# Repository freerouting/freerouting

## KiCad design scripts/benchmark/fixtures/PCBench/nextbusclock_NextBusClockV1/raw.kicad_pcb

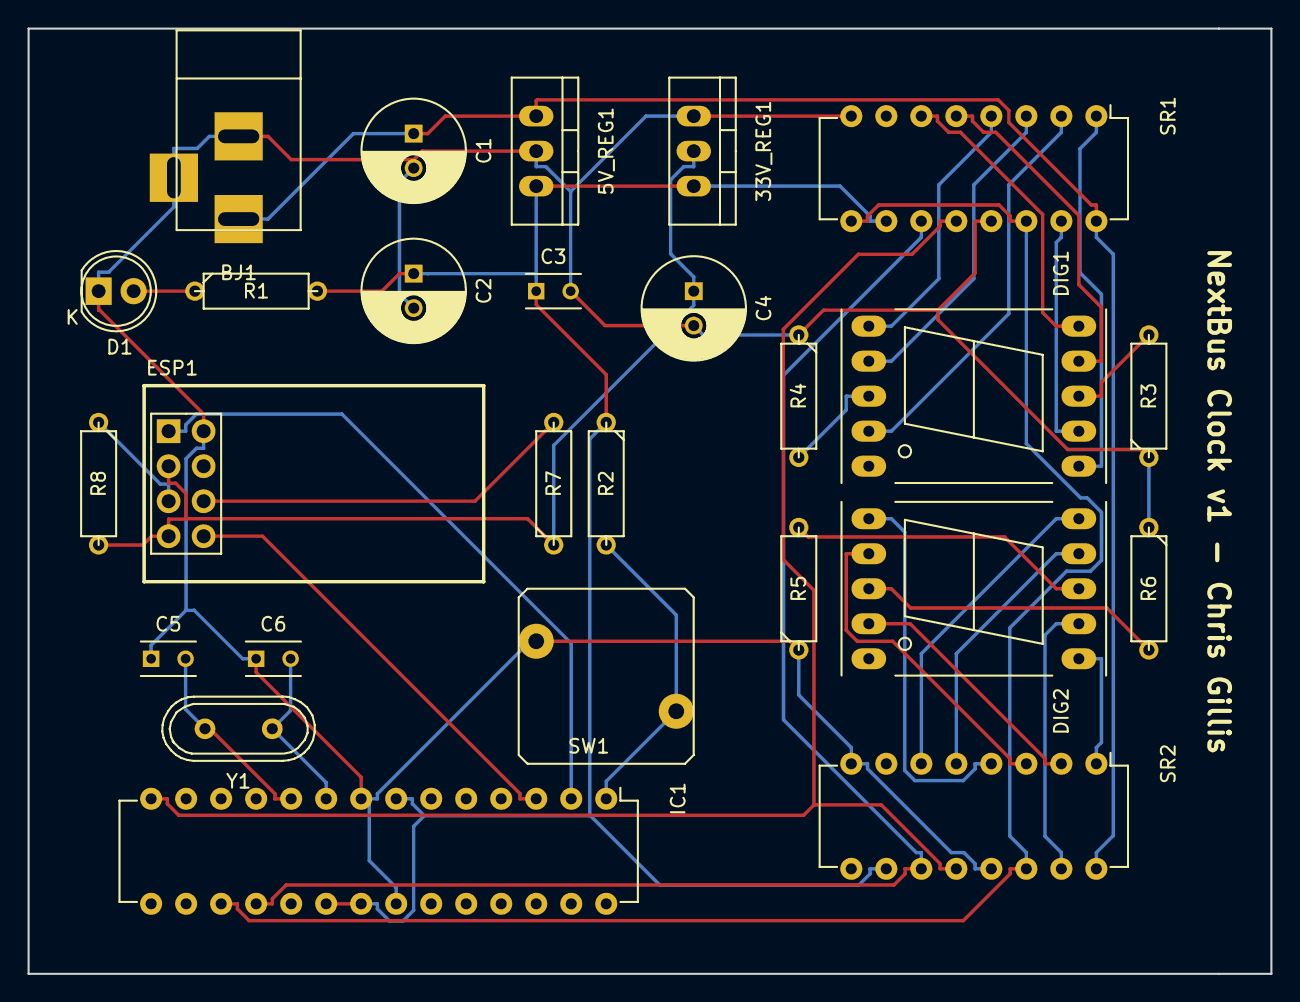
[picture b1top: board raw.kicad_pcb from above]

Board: 2 copper layers, 90.2 x 68.6 mm, 26 parts (0 on the bottom side), 33 nets.

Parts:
5V_REG1: LM7805; TO-220_Neutral123_Vertical
33V_REG1: LD1117V33; TO-220_Neutral123_Vertical
BJ1: BARREL_JACK
C1: 10uF; C_Radial_D7.5_L11.2_P2.5
C2: 1uF; C_Radial_D7.5_L11.2_P2.5
C3: 0.1uf; C_Rect_L4_W2.5_P2.5
C4: 10uf; C_Radial_D7.5_L11.2_P2.5
C5, C6: 22pF; C_Rect_L4_W2.5_P2.5
D1: PWR_LED; LED-5MM
DIG1, DIG2: LTS-6980HR; 7SegmentLED_LTS6760_LTS6780
ESP1: ESP-01
IC1: ATMEGA328-P; DIP-28_W7.62mm
R1: 1k; R3-5
R2, R7, R8: 10k; R3-5
R3, R4, R5, R6: 470; R3-5
SR1, SR2: 74HC595; DIP-16_W7.62mm
SW1: SW_PUSH
Y1: 16MHz; Crystal_HC49-U_Vertical

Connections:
/5V_PWR: 5V_REG1.3, 33V_REG1.3, C2.1, C3.1, IC1.7, IC1.20, IC1.21, R1.2, R2.1, SR1.10, SR2.10
/33V_PWR: 33V_REG1.2, C4.1, ESP1.3, ESP1.7, R7.1, R8.2
/ESP_RX: ESP1.8, IC1.3
/ESP_TX: ESP1.1, IC1.2
/SR_CLOCK: IC1.18, SR1.11, SR2.11
/SR_DATA: IC1.17, SR1.9, SR1.14, SR2.14
/SR_LATCH: IC1.14, SR1.12, SR2.12
GND: 5V_REG1.2, 33V_REG1.1, BJ1.2, BJ1.3, C1.2, C2.2, C3.2, C4.2, C5.1, C6.1, D1.1, ESP1.2, IC1.8, IC1.22, R3.1, R4.1, R5.1, R6.1, SR1.8, SR1.13, SR2.8, SR2.13, SW1.2
unnamed: C5.2, IC1.10, Y1.2
unnamed: C6.2, IC1.9, Y1.1
unnamed: D1.2, R1.1
unnamed: DIG1.1, SR1.4
unnamed: DIG1.2, SR1.3
unnamed: DIG1.3, R4.2
unnamed: DIG1.4, SR1.2
unnamed: DIG1.6, SR1.1
unnamed: DIG1.7, SR1.15
unnamed: DIG1.8, R3.2
unnamed: DIG1.9, SR1.5
unnamed: DIG1.10, SR1.6
unnamed: DIG2.1, SR2.4
unnamed: DIG2.2, SR2.3
unnamed: DIG2.3, R6.2
unnamed: DIG2.4, SR2.2
unnamed: DIG2.6, SR2.1
unnamed: DIG2.7, SR2.15
unnamed: DIG2.8, R5.2
unnamed: DIG2.9, SR2.5
unnamed: DIG2.10, SR2.6
unnamed: ESP1.5, R8.1
unnamed: ESP1.6, R7.2
unnamed: IC1.1, R2.2, SW1.1
VCC: 5V_REG1.1, BJ1.1, C1.1, SR1.16, SR2.16

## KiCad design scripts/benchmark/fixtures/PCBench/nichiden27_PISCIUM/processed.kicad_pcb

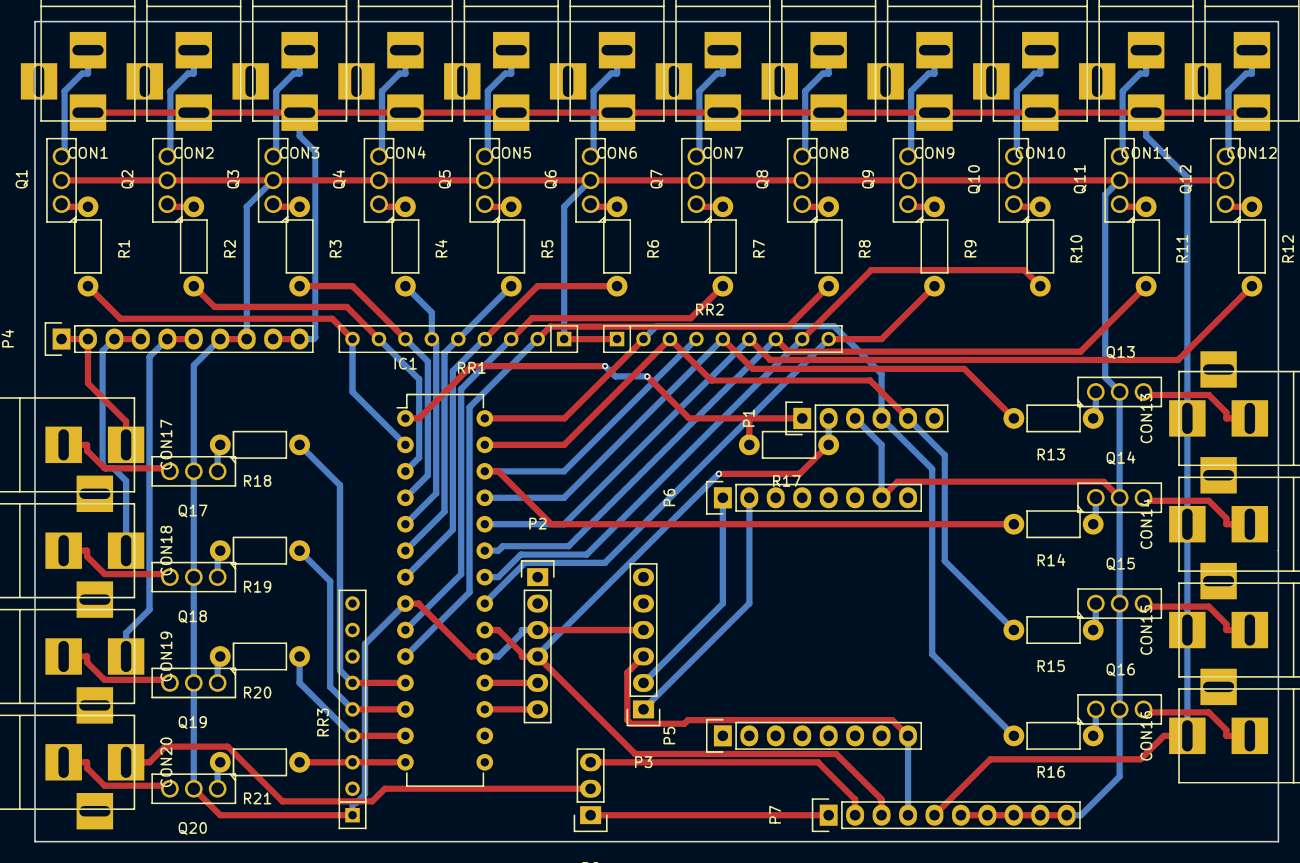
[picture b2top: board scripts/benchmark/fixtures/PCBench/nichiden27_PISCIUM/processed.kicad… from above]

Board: 2 copper layers, 119.4 x 78.7 mm, 73 parts (0 on the bottom side), 75 nets.

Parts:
CON1, CON2, CON3, CON4, CON5, CON6, CON7, CON8, CON9, CON10, CON11, CON12, CON13, CON14, CON15, CON16, CON17, CON18, CON19, CON20: BARREL_JACK
IC1: PIC16F1938; DIP-28_W7.62mm
P1, P2, P3: CONN_01X06; Pin_Header_Straight_1x06
P4, P7: CONN_01X10; Pin_Header_Straight_1x10
P5, P6: CONN_01X08; Pin_Header_Straight_1x08
P8: GINGA_voltage_selector; Pin_Header_Straight_1x03
Q1, Q2, Q3, Q4, Q5, Q6, Q7, Q8, Q9, Q10, Q11, Q12, Q13, Q14, Q15, Q16, Q17, Q18, Q19, Q20: EKI04047; SOT126_SOT32_Housing_Vertical
R1, R2, R3, R4, R5, R6, R7, R8, R9, R10, R11, R12, R13, R14, R15, R16, R18, R19, R20, R21: 100; Resistor_Horizontal_RM7mm
R17: 4.7k-10k; Resistor_Horizontal_RM7mm
RR1, RR2, RR3: RR8_100k; Resistor_Array_SIP8

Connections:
3.3V_LOGIC: P3.3, P5.8, P7.4
5V_GINGA: P7.1, P8.1
5V_ITTOU1: CON19.1, P4.5, P4.6
5V_LOGIC: IC1.20, P1.2, P2.4, P7.3, R17.1
12V_GINGA: P7.2, P8.3
12V_KOUTOU11: CON17.1, P4.1, P4.2
12V_KOUTOU21: CON18.1, P4.3, P4.4
12V_SEIZAE1: CON1.1, CON2.1, CON3.1, CON4.1, CON5.1, CON6.1, CON7.1, CON8.1, CON9.1, CON10.1, CON11.1, CON12.1, CON13.1, CON14.1, CON15.1, CON16.1, P4.9, P4.10, P7.5
+12V: IC1.8, IC1.19, P1.3, P2.3, P3.4, P4.7, P4.8, P6.7, P7.6, P7.7, P7.8, P7.9, P7.10, Q1.2, Q2.2, Q3.2, Q4.2, Q5.2, Q6.2, Q7.2, Q8.2, Q9.2, Q10.2, Q11.2, Q12.2, Q13.2, Q14.2, Q15.2, Q16.2, Q17.2, Q18.2, Q19.2, Q20.2, RR1.1, RR2.1, RR3.1
unnamed: CON1.2, Q1.3
unnamed: CON2.2, Q2.3
unnamed: CON3.2, Q3.3
unnamed: CON4.2, Q4.3
unnamed: CON5.2, Q5.3
unnamed: CON6.2, Q6.3
unnamed: CON7.2, Q7.3
unnamed: CON8.2, Q8.3
unnamed: CON9.2, Q9.3
unnamed: CON10.2, Q10.3
unnamed: CON11.2, Q11.3
unnamed: CON12.2, Q12.3
unnamed: CON13.2, Q13.3
unnamed: CON14.2, Q14.3
unnamed: CON15.2, Q15.3
unnamed: CON16.2, Q16.3
unnamed: CON17.2, Q17.3
unnamed: CON18.2, Q18.3
unnamed: CON19.2, Q19.3
unnamed: CON20.2, Q20.3
unnamed: IC1.1, P1.1, R17.2
unnamed: IC1.2, R1.2, RR1.9
unnamed: IC1.3, R2.2, RR1.8
unnamed: IC1.4, R3.2, RR1.7
unnamed: IC1.5, R4.2, RR1.6
unnamed: IC1.6, R5.2, RR1.5
unnamed: IC1.7, R6.2, RR1.4
unnamed: IC1.9, R7.2, RR1.3
unnamed: IC1.10, R8.2, RR1.2
unnamed: IC1.11, R18.1, RR3.6
unnamed: IC1.12, R19.1, RR3.5
unnamed: IC1.13, R20.1, RR3.4
unnamed: IC1.14, R21.1, RR3.3
unnamed: IC1.17, P2.6
unnamed: IC1.18, P2.5
unnamed: IC1.21, R9.2, RR2.9
unnamed: IC1.22, R10.2, RR2.8
unnamed: IC1.23, R11.2, RR2.7
unnamed: IC1.24, R12.2, RR2.6
unnamed: IC1.25, R13.2, RR2.5
unnamed: IC1.26, R14.2, RR2.4
unnamed: IC1.27, P1.5, R15.2, RR2.3
unnamed: IC1.28, P1.4, R16.2, RR2.2
unnamed: P3.1, P6.2
unnamed: P3.2, P6.1
unnamed: Q1.1, R1.1
unnamed: Q2.1, R2.1
unnamed: Q3.1, R3.1
unnamed: Q4.1, R4.1
unnamed: Q5.1, R5.1
unnamed: Q6.1, R6.1
unnamed: Q7.1, R7.1
unnamed: Q8.1, R8.1
unnamed: Q9.1, R9.1
unnamed: Q10.1, R10.1
unnamed: Q11.1, R11.1
unnamed: Q12.1, R12.1
unnamed: Q13.1, R13.1
unnamed: Q14.1, R14.1
unnamed: Q15.1, R15.1
unnamed: Q16.1, R16.1
unnamed: Q17.1, R18.2
unnamed: Q18.1, R19.2
unnamed: Q19.1, R20.2
unnamed: Q20.1, R21.2
VCC_GINGA: CON20.1, P8.2

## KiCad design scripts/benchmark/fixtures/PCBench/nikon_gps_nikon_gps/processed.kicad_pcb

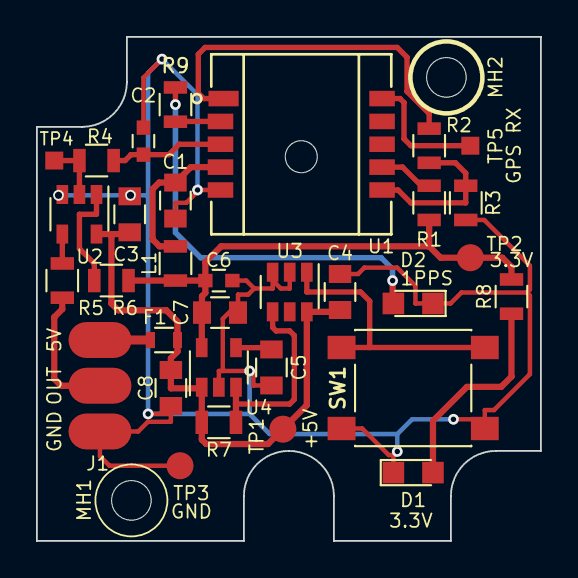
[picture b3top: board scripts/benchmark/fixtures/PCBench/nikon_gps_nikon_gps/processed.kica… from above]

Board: 2 copper layers, 28.0 x 28.0 mm, 34 parts (0 on the bottom side), 20 nets.

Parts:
C1, C3, C4: 100nF; C_0805
C2: 18pF; C_0603
C5: 470pF; C_0805
C6: 1nF; C_0603
C7, C8: 10uF; C_0805
D1: Red; LED_0805
D2: Blue; LED_0805
F1: 0.1A; R_0603
J1: Conn_01x03; Connection_Pads_03
L1: 600Ohm; L_0805
MH1, MH2: M2 screw; MountingHole_2.2mm_M2_DIN965
R1, R3: 10K; R_0805
R2, R4, R5: 33; R_0805
R6, R7: 0; R_0805
R8: 330; R_0805
R9: 270; R_0805
SW1: ON/OFF; SW_SPST_PTS645
TP1: 5V; Measurement_Point_Round-SMD-Pad_Small
TP2: 3.3V; Measurement_Point_Round-SMD-Pad_Small
TP3: GND; Measurement_Point_Round-SMD-Pad_Small
TP4: GPS TX; Measurement_Point_Square-SMD_1.0mmx1.0mm
TP5: GPS RX; Measurement_Point_Square-SMD_1.0mmx1.0mm
U1: Hornet ORG1411; ORG1411_GPS
U2: SN74LV1T126_ALT; SOT-23-5
U3: MAX16054; SOT-23-6
U4: MIC5205-3.3; SOT-23-5

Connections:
+3V3: C6.1, C7.1, L1.2, R1.1, R6.1, R8.2, TP2.1, U4.5
+5V: C3.2, C4.2, C8.1, F1.1, R7.2, TP1.1, U2.5, U3.6, U4.1
/1PPS: R9.2, U1.2
/3.3V_EN: R7.1, U3.4, U4.3
/3.3V_GPS: C1.2, L1.1, U1.4
/BUF_EN: R6.2, U2.1
/BUF_IN: R4.2, TP4.1, U2.2
/BUF_OUT: R5.1, U2.4
/C_BYP: C5.1, U4.4
/GPS_OUT: J1.2, R5.2
/GPS_RX: TP5.1, U1.10
/GPS_TX: C2.1, R4.1, U1.3
/ON_OFF: R2.2, U1.1
/ON_SW: SW1.2, U3.1
/WAKEUP: R2.1, R3.1, U1.6
/~CTS: R1.2, U1.7
GND: C1.1, C2.2, C3.1, C4.1, C5.2, C6.2, C7.2, C8.2, D1.1, D2.1, J1.3, R3.2, SW1.1, TP3.1, U1.5, U2.3, U3.2, U3.3, U4.2
unnamed: D1.2, R8.1
unnamed: D2.2, R9.1
unnamed: F1.2, J1.1
